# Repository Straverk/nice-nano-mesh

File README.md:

# nice-nano-mesh
PCB for nice!nano board with microcontroller

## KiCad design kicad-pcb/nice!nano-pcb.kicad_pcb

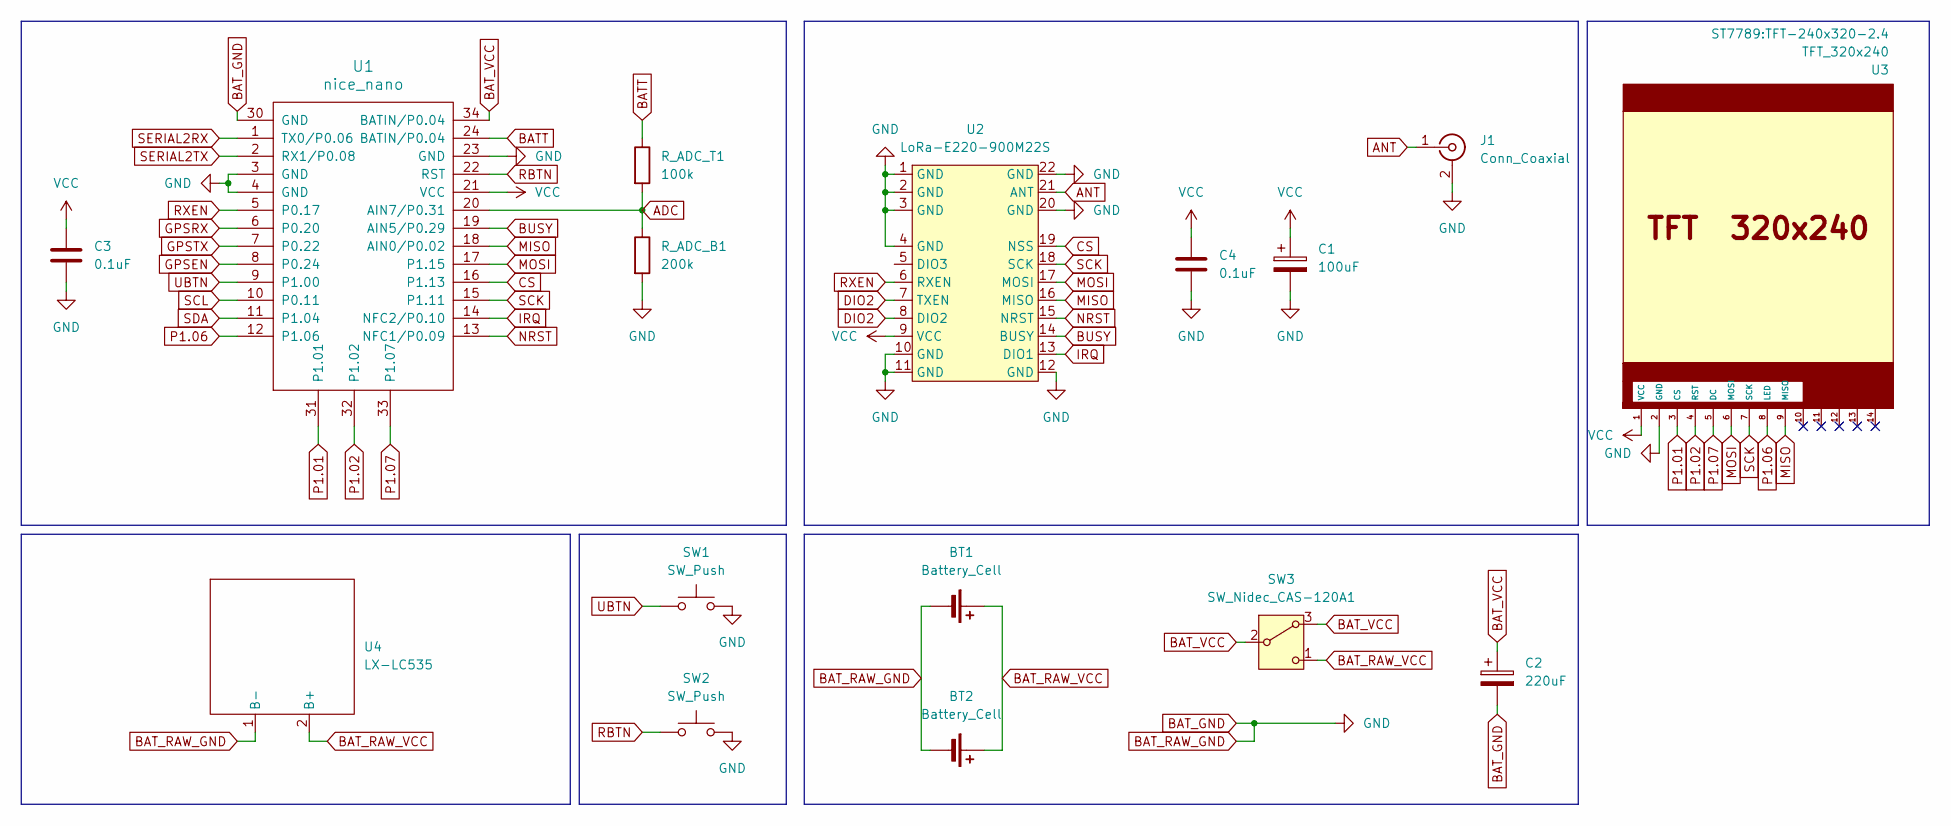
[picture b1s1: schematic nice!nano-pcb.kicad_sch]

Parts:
BT1, BT2: Battery_Cell; BatteryHolder_Keystone_1042_1x18650
C1: 100uF; C_Elec_5x5.8
C2: 220uF; C_Elec_6.3x7.7
C3, C4: 0.1uF; C_1206_3216Metric_Pad1.33x1.80mm_HandSolder
J1: Conn_Coaxial; SMA_Samtec_SMA-J-P-H-ST-EM1_EdgeMount
R_ADC_B1: 200k; R_Axial_DIN0207_L6.3mm_D2.5mm_P7.62mm_Horizontal
R_ADC_T1: 100k; R_Axial_DIN0207_L6.3mm_D2.5mm_P7.62mm_Horizontal
SW1, SW2: SW_Push; SW_Push_1TS009xxxx-xxxx-xxxx_6x6x5mm
SW3: SW_Nidec_CAS-120A1; SW_Slide_SPDT_Angled_CK_OS102011MA1Q
U1: nice_nano
U2: LoRa-E220-900M22S
U3: TFT_320x240; TFT-240x320-2.4
U4: LX-LC535

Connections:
ADC: R_ADC_B1.1, R_ADC_T1.2, U1.20 (AIN7/P0.31)
ANT: J1.1 (In), U2.21 (ANT)
BATT: R_ADC_T1.1, U1.24 (BATIN/P0.04)
BAT_GND: BT1.2 (-), BT2.2 (-), C1.2, C2.2, C3.2, C4.2, J1.2 (Ext), R_ADC_B1.2, SW1.2, SW2.2, U1.3 (GND), U1.4 (GND), U1.23 (GND), U1.30 (GND), U2.1 (GND), U2.2 (GND), U2.3 (GND), U2.4 (GND), U2.10 (GND), U2.11 (GND), U2.12 (GND), U2.20 (GND), U2.22 (GND), U3.2 (GND), U4.1 (B-)
BAT_RAW_VCC: BT1.1 (+), BT2.1 (+), SW3.1 (C), U4.2 (B+)
BAT_VCC: C2.1, SW3.2 (B), SW3.3 (A), U1.34 (BATIN/P0.04)
BUSY: U1.19 (AIN5/P0.29), U2.14 (BUSY)
CS: U1.16 (P1.13), U2.19 (NSS)
DIO2: U2.7 (TXEN), U2.8 (DIO2)
GPSEN: U1.8 (P0.24)
GPSRX: U1.6 (P0.20)
GPSTX: U1.7 (P0.22)
IRQ: U1.14 (NFC2/P0.10), U2.13 (DIO1)
MISO: U1.18 (AIN0/P0.02), U2.16 (MISO), U3.9 (MISO)
MOSI: U1.17 (P1.15), U2.17 (MOSI), U3.6 (MOSI)
NRST: U1.13 (NFC1/P0.09), U2.15 (NRST)
P1.01: U1.31 (P1.01), U3.3 (CS)
P1.02: U1.32 (P1.02), U3.4 (RST)
P1.06: U1.12 (P1.06), U3.8 (LED)
P1.07: U1.33 (P1.07), U3.5 (DC)
RBTN: SW2.1, U1.22 (RST)
RXEN: U1.5 (P0.17), U2.6 (RXEN)
SCK: U1.15 (P1.11), U2.18 (SCK), U3.7 (SCK)
SCL: U1.10 (P0.11)
SDA: U1.11 (P1.04)
SERIAL2RX: U1.1 (TX0/P0.06)
SERIAL2TX: U1.2 (RX1/P0.08)
UBTN: SW1.1, U1.9 (P1.00)
VCC: C1.1, C3.1, C4.1, U1.21 (VCC), U2.9 (VCC), U3.1 (VCC)

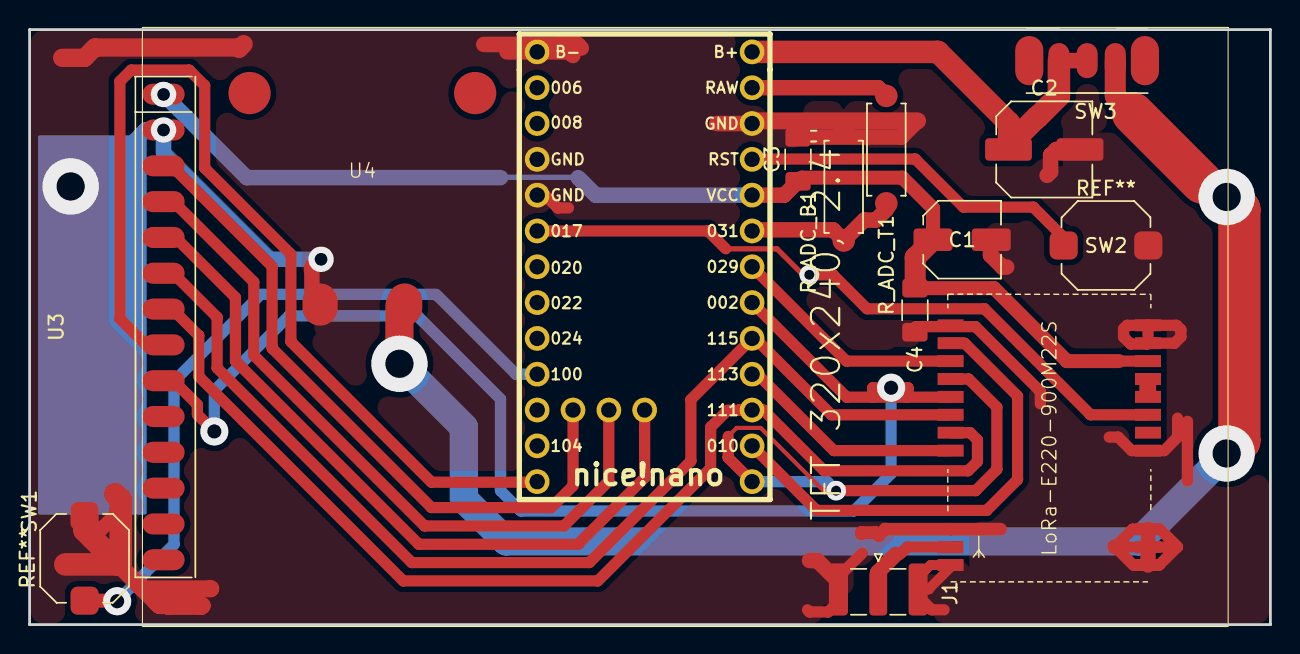
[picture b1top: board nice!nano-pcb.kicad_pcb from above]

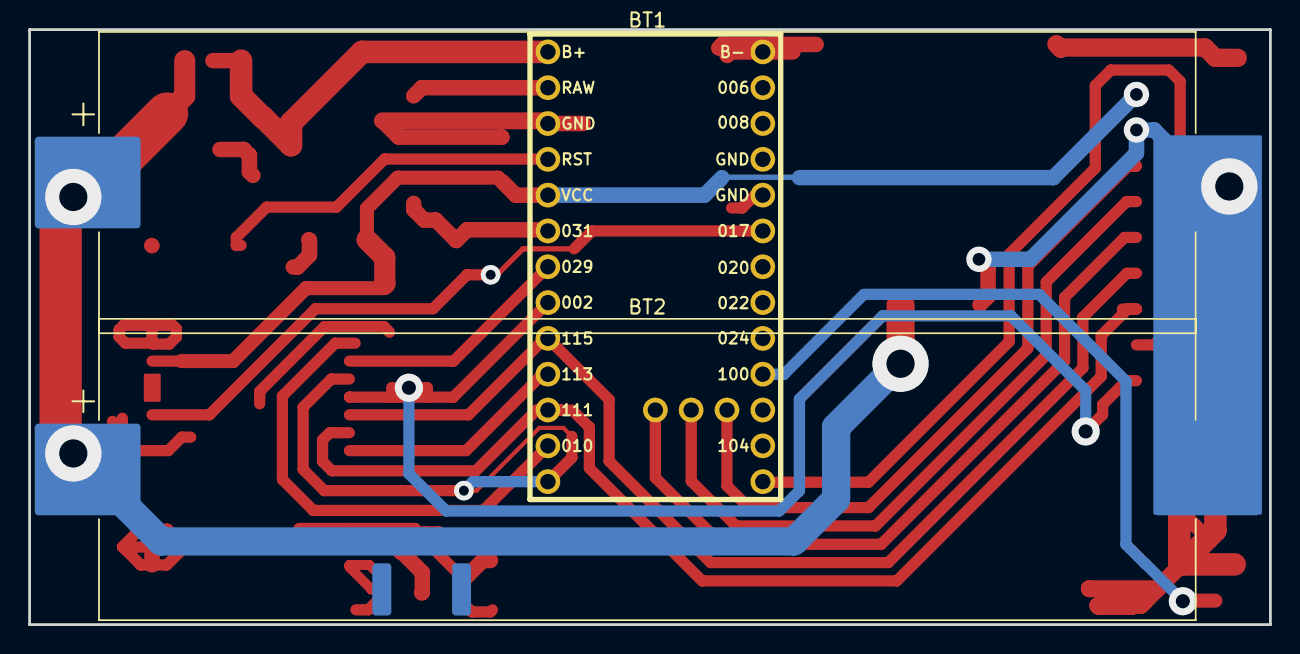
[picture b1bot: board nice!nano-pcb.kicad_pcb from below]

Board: 2 copper layers, 88.0 x 42.2 mm, 16 parts (2 on the bottom side), 22 nets.

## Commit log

2026-02-17 Backup
2026-02-23 Setup paths, delete superfluous
2026-02-23 Setup fill ground, small fixes
2026-02-24 Move antenna coaxial
2026-04-08 Final edits
2026-05-19 Update LICENSE
2026-05-19 Wrap components to submodules
